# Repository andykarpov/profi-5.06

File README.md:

# Unofficial Profi 5.06 repository 

Mainboard forum: http://zx-pk.ru/threads/21644-plata-protsessora-profi-v5-06.html
Upperboard forum: http://zx-pk.ru/threads/21356-plata-periferii-profi-v5-06.html

## Ветка mega_real_spi

Данная ветка содержит экспериметнальную прошивку для CPLD и новую реализацию контроллера клавиатуры / мыши / RTC.

Отличительные особенности реализации:
- безвейтовость
- работа клавиатуы в турбо-режимах
- работа всех функциональных кнопок
- реализация профиковского стандарта XT клавиатуры и стандартного ZX Spectrum режима
- поддержка мыши (2-,3-кнопочных, со скроллером и без)
- поддержка RTC (только чтение регистров времени и даты)

Контроллер клавиатуры собран на дополнительной платке (на базе Atmega328) без доработок платы верхушки. 

## Принцип работы

Функция контроллера - получить данные от PS/2 клавиатуры и мыши и передать их по SPI протоколу в виде матрицы 
состояний механической клавиатуры ZX Spectrum + нескольких байт координат от мыши. Всю остальную работу берет на себя CPLD, моментально декодируя данные и подставляя готовые состояния при дешифрации порта #FE. Скорость потока от МК к CPLD составляет около 1кГц. Если подключена мышь - скорость потока немного снижается, но по ощущениям - это никак не влияет на скорость работы клавиатуры.

### Специальные клавиши и клавиатурные комбинации
- Scroll Lock: переключает turbo режим, значение сохраняется в энергонезависимой памяти
- Print Screen: переключает раскладку клавиатуры profi / zx spectrum
- Ctrl+Alt+Del: формирует сигнал сброса 
- Ctrl+Alt+Backpace: принудительная переинициализация контроллера
- Ctrl+Alt+Esc: кнопка Magic

### Установка даты и времени RTC часиков верхушки
Так как в контроллере не реализована эмуляция RTC в полной мере (только чтение), для установки времени можно воспользоваться последовательным соединением с контроллером.
Реализованные команды:
- HELP выведет встроенную подсказку
- GET выведет текущее время
- SET YYYY MM DD HH II SS W установит RTC в заданную дату/время/день недели

## Контроллер на базе Atmega328

Данный контроллер собирается в виде отдельной платки, которая вставляется в панельку вместо Atmega8515. Контроллер выполнен на базе МК Atmega328.Программирование осуществляется из среды Arduino IDE 1.6.1 или выше. Никакие модификации платы верхушки не требуются.

## Готовые прошивки
Готовые hex-файлы для прошивки с помощью программатора готовы и доступны из git-репозитария.

Fuse биты для Atmega328:
Low Fuse	0xFF
High Fuse	0xDA
Extended Fuse	0x05

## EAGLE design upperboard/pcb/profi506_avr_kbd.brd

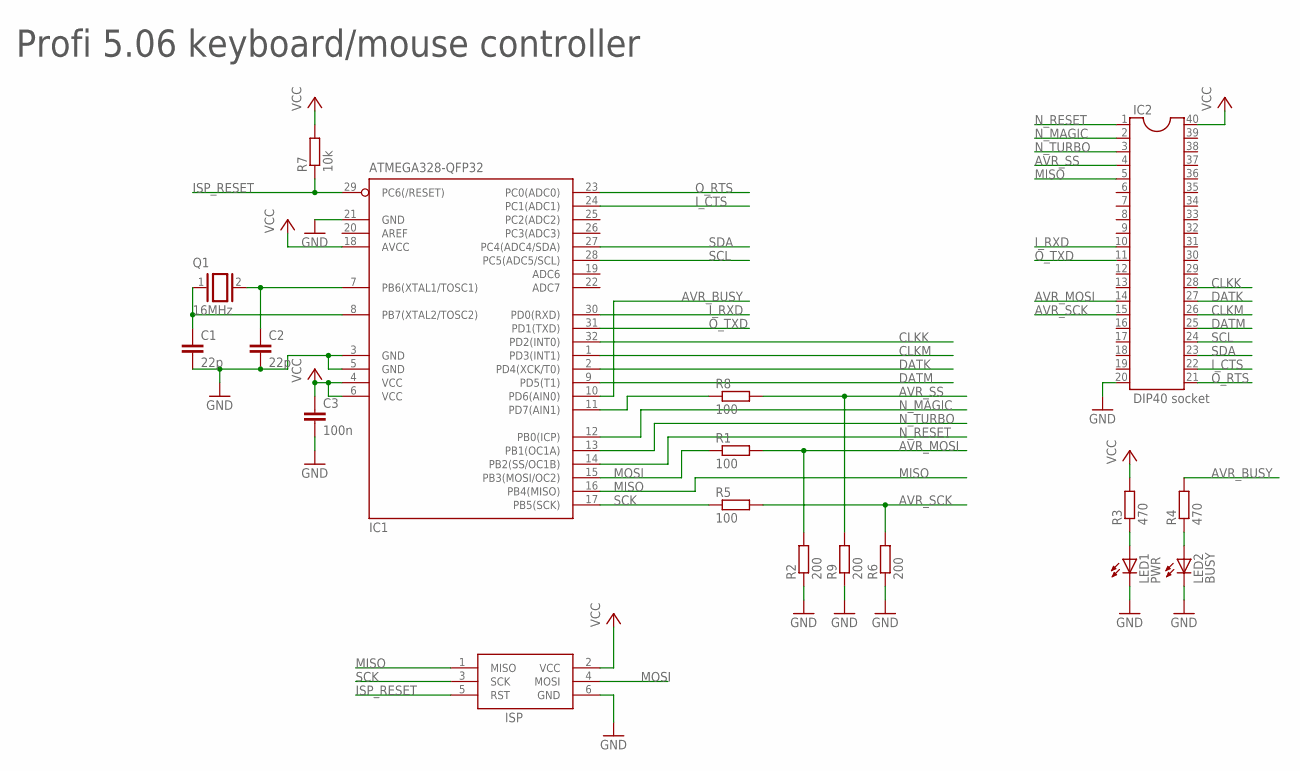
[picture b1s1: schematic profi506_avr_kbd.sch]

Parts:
C1, C2: 22p; C0805
C3: 100n; C0805
IC1: ATMEGA328-QFP32; TQFP32-08
IC2: DIP40 socket; DIL40
ISP: AVRISP-BOX
LED1: PWR; CHIPLED_0805
LED2: BUSY; CHIPLED_0805
Q1: 16MHz; QS
R1, R5, R8: 100; R0805
R2, R6, R9: 200; R0805
R3, R4: 470; R0805
R7: 10k; R0805

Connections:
AVR_BUSY: IC1.10 (PD6(AIN0)), R4.2
AVR_MOSI: IC2.14, R1.2, R2.2
AVR_SCK: IC2.15, R5.2, R6.2
AVR_SS: IC2.4, R8.2, R9.2
CLKK: IC1.32 (PD2(INT0)), IC2.28
CLKM: IC1.1 (PD3(INT1)), IC2.26
DATK: IC1.2 (PD4(XCK/T0)), IC2.27
DATM: IC1.9 (PD5(T1)), IC2.25
GND: C1.2, C2.2, C3.2, IC1.3 (GND), IC1.5 (GND), IC1.21 (GND), IC2.20, ISP.6 (GND), LED1.C, LED2.C, R2.1, R6.1, R9.1
ISP_RESET: IC1.29 (PC6(/RESET)), ISP.5 (RST), R7.1
I_CTS: IC1.24 (PC1(ADC1)), IC2.22
I_RXD: IC1.30 (PD0(RXD)), IC2.10
MISO: IC1.16 (PB4(MISO)), IC2.5, ISP.1 (MISO)
MOSI: IC1.15 (PB3(MOSI/OC2)), ISP.4 (MOSI), R1.1
unnamed: C2.1, IC1.7 (PB6(XTAL1/TOSC1)), Q1.2
unnamed: C1.1, IC1.8 (PB7(XTAL2/TOSC2)), Q1.1
unnamed: IC1.11 (PD7(AIN1)), R8.1
unnamed: LED1.A, R3.1
unnamed: LED2.A, R4.1
N_MAGIC: IC1.12 (PB0(ICP)), IC2.2
N_RESET: IC1.14 (PB2(SS/OC1B)), IC2.1
N_TURBO: IC1.13 (PB1(OC1A)), IC2.3
O_RTS: IC1.23 (PC0(ADC0)), IC2.21
O_TXD: IC1.31 (PD1(TXD)), IC2.11
SCK: IC1.17 (PB5(SCK)), ISP.3 (SCK), R5.1
SCL: IC1.28 (PC5(ADC5/SCL)), IC2.24
SDA: IC1.27 (PC4(ADC4/SDA)), IC2.23
VCC: C3.1, IC1.4 (VCC), IC1.6 (VCC), IC1.18 (AVCC), IC2.40, ISP.2 (VCC), R3.2, R7.2

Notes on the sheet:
Profi 5.06 keyboard/mouse controller

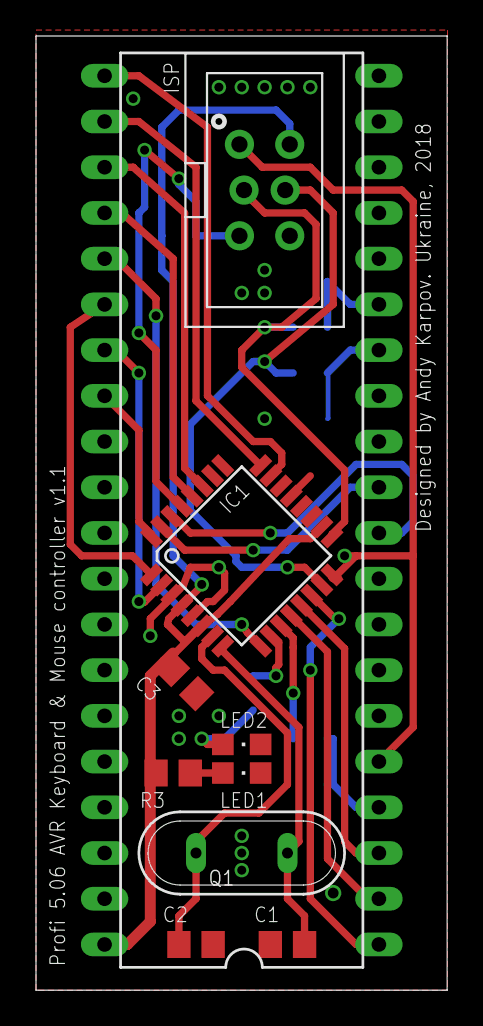
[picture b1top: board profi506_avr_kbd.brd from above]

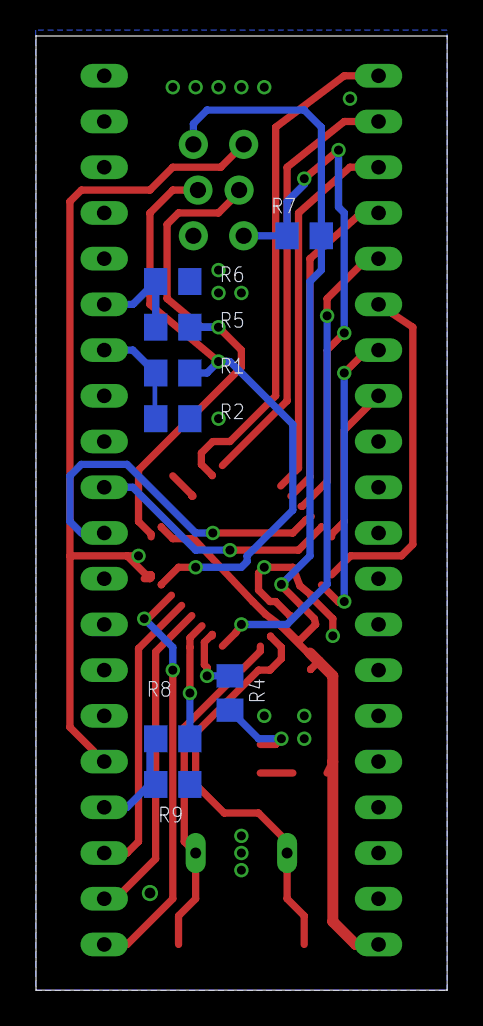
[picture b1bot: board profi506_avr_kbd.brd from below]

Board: 2 copper layers, 22.8 x 53.0 mm, 19 parts (8 on the bottom side), 28 nets.

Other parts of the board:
U$1: OSHWLOGO_TOL_0.2

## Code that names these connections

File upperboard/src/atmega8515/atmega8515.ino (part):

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#define DEBUG_MODE 1

// ---- Pins for Atmega328 ----
#define PIN_KBD_CLK 2 // pin 28 (CLKK)
#define PIN_KBD_DAT 4 // pin 27 (DATK)

#define PIN_MOUSE_CLK 3 // pin 26 (CLKM)
#define PIN_MOUSE_DAT 5 // pin 25 (DATM)

#define PIN_AVR_CLK 11 // pin 14 (ATM_ADR0 - CPLD PIN 102)
#define PIN_AVR_RST 12 // pin 5 (ATM_PB4 - CPLD PIN 123)
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// Profi upper board modifications:
// 1) replace crystal with 16MHz
// 2) add wire between D34:28 and D34:13
#define PIN_KBD_CLK_ORIG 23 // pin 28 (CLKK)
#define PIN_KBD_CLK 11 // pin 13 must be connected to pin 28.
#define PIN_KBD_DAT 22 // pin 27 (DATK)

#define PIN_MOUSE_CLK 21 // pin 26 (CLKM)
#define PIN_MOUSE_DAT 20 // pin 25 (DATM)

#define PIN_AVR_CLK 12 // pin 14 (ATM_ADR0 - CPLD PIN 102)
#define PIN_AVR_RST 4 // pin 5 (ATM_PB4 - CPLD PIN 123)
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
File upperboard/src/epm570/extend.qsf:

# -------------------------------------------------------------------------- #
#
# Copyright (C) 1991-2009 Altera Corporation
# Your use of Altera Corporation's design tools, logic functions 
# and other software and tools, and its AMPP partner logic 
# functions, and any output files from any of the foregoing 
# (including device programming or simulation files), and any 
# associated documentation or information are expressly subject 
# to the terms and conditions of the Altera Program License 
# Subscription Agreement, Altera MegaCore Function License 
# Agreement, or other applicable license agreement, including, 
# without limitation, that your use is for the sole purpose of 
# programming logic devices manufactured by Altera and sold by 
# Altera or its authorized distributors.  Please refer to the 
# applicable agreement for further details.
#
# -------------------------------------------------------------------------- #
#
# Quartus II
# Version 9.1 Build 222 10/21/2009 SJ Full Version
# Date created = 16:20:46  August 09, 2012
#
# -------------------------------------------------------------------------- #
#
# Notes:
#
# 1) The default values for assignments are stored in the file:
#		extend_assignment_defaults.qdf
#    If this file doesn't exist, see file:
#		assignment_defaults.qdf
#
# 2) Altera recommends that you do not modify this file. This
#    file is updated automatically by the Quartus II software
#    and any changes you make may be lost or overwritten.
#
# -------------------------------------------------------------------------- #


set_global_assignment -name FAMILY "MAX II"
set_global_assignment -name DEVICE EPM570T144C5
set_global_assignment -name TOP_LEVEL_ENTITY extend
set_global_assignment -name ORIGINAL_QUARTUS_VERSION 9.1
set_global_assignment -name PROJECT_CREATION_TIME_DATE "16:20:46  AUGUST 09, 2012"
set_global_assignment -name LAST_QUARTUS_VERSION "13.0 SP1"
set_global_assignment -name USE_GENERATED_PHYSICAL_CONSTRAINTS OFF -section_id eda_blast_fpga
set_global_assignment -name DEVICE_FILTER_PACKAGE TQFP
set_global_assignment -name DEVICE_FILTER_PIN_COUNT 144
set_global_assignment -name DEVICE_FILTER_SPEED_GRADE 5
set_global_assignment -name MAX7000_DEVICE_IO_STANDARD "3.3-V LVTTL"
set_location_assignment PIN_2 -to reset
set_location_assignment PIN_98 -to nmi
set_location_assignment PIN_85 -to intr
set_location_assignment PIN_75 -to cswg
set_location_assignment PIN_84 -to drq
set_location_assignment PIN_74 -to dden
set_location_assignment PIN_73 -to wf_de
set_location_assignment PIN_80 -to wd
set_location_assignment PIN_79 -to tr43
set_location_assignment PIN_72 -to rawr
set_location_assignment PIN_71 -to rclk
set_location_assignment PIN_70 -to wg_clk
set_location_assignment PIN_69 -to hlt
set_location_assignment PIN_78 -to sl
set_location_assignment PIN_77 -to sr
set_location_assignment PIN_76 -to rst
set_location_assignment PIN_81 -to rdat
set_location_assignment PIN_68 -to side1
set_location_assignment PIN_67 -to wdat
set_location_assignment PIN_66 -to disk1
set_location_assignment PIN_63 -to disk0
set_location_assignment PIN_45 -to bc1a
set_location_assignment PIN_49 -to bdira
set_location_assignment PIN_48 -to bc1b
set_location_assignment PIN_50 -to bdirb
set_location_assignment PIN_91 -to magik
set_location_assignment PIN_86 -to f8
set_location_assignment PIN_130 -to SD_CLK
set_location_assignment PIN_95 -to w_a_i_t
set_global_assignment -name SYNTH_TIMING_DRIVEN_SYNTHESIS OFF
set_global_assignment -name OPTIMIZE_HOLD_TIMING OFF
set_global_assignment -name FITTER_EFFORT "STANDARD FIT"
set_location_assignment PIN_31 -to Data[0]
set_location_assignment PIN_30 -to Data[1]
set_location_assignment PIN_29 -to Data[2]
set_location_assignment PIN_24 -to Data[3]
set_location_assignment PIN_23 -to Data[4]
set_location_assignment PIN_27 -to Data[5]
set_location_assignment PIN_28 -to Data[6]
set_location_assignment PIN_32 -to Data[7]
set_location_assignment PIN_13 -to adress[0]
set_location_assignment PIN_12 -to adress[1]
set_location_assignment PIN_11 -to adress[2]
set_location_assignment PIN_8 -to adress[3]
set_location_assignment PIN_141 -to adress[4]
set_location_assignment PIN_142 -to adress[5]
set_location_assignment PIN_143 -to adress[6]
set_location_assignment PIN_144 -to adress[7]
set_location_assignment PIN_139 -to adress[8]
set_location_assignment PIN_138 -to adress[9]
set_location_assignment PIN_137 -to adress[10]
set_location_assignment PIN_15 -to adress[12]
set_location_assignment PIN_134 -to adress[11]
set_location_assignment PIN_16 -to adress[13]
set_location_assignment PIN_18 -to adress[14]
set_location_assignment PIN_20 -to adress[15]
set_location_assignment PIN_97 -to iorqge
set_global_assignment -name MIN_CORE_JUNCTION_TEMP 0
set_global_assignment -name MAX_CORE_JUNCTION_TEMP 85
set_global_assignment -name POWER_EXT_SUPPLY_VOLTAGE_TO_REGULATOR 3.3V
set_global_assignment -name INCREMENTAL_COMPILATION OFF
set_global_assignment -name LL_ROOT_REGION ON -section_id "Root Region"
set_global_assignment -name LL_MEMBER_STATE LOCKED -section_id "Root Region"
set_global_assignment -name STRATIX_DEVICE_IO_STANDARD "3.3-V LVTTL"
set_location_assignment PIN_6 -to rom14
set_location_assignment PIN_1 -to cpm
set_location_assignment PIN_21 -to t_ap6
set_location_assignment PIN_22 -to oe_ap6
set_location_assignment PIN_37 -to t_lvc245
set_location_assignment PIN_38 -to saa_cs
set_location_assignment PIN_39 -to saa_a0
set_location_assignment PIN_40 -to saa_clk
set_location_assignment PIN_41 -to dac2_cs
set_location_assignment PIN_42 -to dac
set_location_assignment PIN_43 -to dac1_cs
set_location_assignment PIN_44 -to vv55_cs
set_location_assignment PIN_52 -to blok
set_location_assignment PIN_53 -to cache_we
set_location_assignment PIN_55 -to lwr
set_location_assignment PIN_57 -to vi53_cs
set_location_assignment PIN_59 -to ladr5
set_location_assignment PIN_58 -to ladr6
set_location_assignment PIN_60 -to vv51_cs
set_location_assignment PIN_61 -to rxrdt
set_location_assignment PIN_62 -to txrdt
set_location_assignment PIN_87 -to timer
set_location_assignment PIN_93 -to ri
set_location_assignment PIN_94 -to dcd
set_location_assignment PIN_104 -to SEL
set_location_assignment PIN_105 -to INT0
set_location_assignment PIN_96 -to int
set_location_assignment PIN_106 -to hdd_a0
set_location_assignment PIN_107 -to hdd_a1
set_location_assignment PIN_108 -to hdd_a2
set_location_assignment PIN_109 -to hdd_wr
set_location_assignment PIN_110 -to hdd_cs1
set_location_assignment PIN_111 -to hdd_cs0
set_location_assignment PIN_112 -to hdd_rd
set_location_assignment PIN_113 -to hdd_rh_oe
set_location_assignment PIN_114 -to hdd_rh_c
set_location_assignment PIN_117 -to hdd_wh_oe
set_location_assignment PIN_118 -to hdd_wh_c
set_location_assignment PIN_119 -to hdd_rwl_t
set_location_assignment PIN_120 -to c_dffd
set_location_assignment PIN_127 -to turbo
set_location_assignment PIN_14 -to zx14mhz
set_location_assignment PIN_133 -to tr_dos
set_location_assignment PIN_129 -to SD_DO
set_location_assignment PIN_132 -to SD_CS
set_location_assignment PIN_131 -to SD_DI
set_location_assignment PIN_3 -to wr_z
set_location_assignment PIN_4 -to rd_z
set_location_assignment PIN_7 -to mrq_z
set_location_assignment PIN_5 -to iorq_z
set_location_assignment PIN_140 -to m1_z
set_location_assignment PIN_124 -to iorqge_sl
set_location_assignment PIN_51 -to cache_oe
set_location_assignment PIN_122 -to ay_clk
set_location_assignment PIN_121 -to cpld_121

set_location_assignment PIN_101 -to INT1
set_global_assignment -name POWER_PRESET_COOLING_SOLUTION "NO HEAT SINK WITH STILL AIR"
set_location_assignment PIN_125 -to AVR_SS
set_location_assignment PIN_123 -to AVR_MISO
set_location_assignment PIN_102 -to AVR_MOSI
set_location_assignment PIN_103 -to AVR_SCK
set_global_assignment -name VHDL_FILE mc146818a.vhd
set_global_assignment -name VHDL_FILE spi_slave.vhd
set_global_assignment -name VHDL_FILE cpld_kbd.vhd
set_global_assignment -name VHDL_FILE SPI.vhd
set_global_assignment -name VHDL_FILE extend.vhd
set_global_assignment -name VECTOR_WAVEFORM_FILE extend.vwf

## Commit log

2018-03-20 Updated upperboard pdf, renamed zxmc2 firmware hex, added upperboard pcb sources
2018-03-20 added links to the forums
2018-03-20 Expiremental functionality: reading ports 7ffd and dffd from trdos
2018-03-20 Expirimental branch to decode keyboard on cpld side, atmega firmware will be rewritten
2018-03-20 Experimental branch with cutted out Atmega8515 support
2018-03-20 Experimenail branch with mouse support inside CPLD without atmega
2018-03-20 added pcb revisions RevA and RevB
2018-03-21 Merge
2018-03-25 Added implementation of atmega328p replacement for ps/2 keyboard / mouse controller. Initial revision
2018-03-26 port FE selector fixes
2018-03-26 fixed port FE
2018-03-26 fixed kb decoding
2018-03-26 added clock and cs to cpld_kbd
2018-03-26 fixed bug :)
2018-03-26 latest firmware
2018-03-26 fixed profi keyboard decoding
2018-03-27 added turbo, mode change and reset
2018-03-28 Added pin INT1 as input
2018-03-28 Changed mouse data packet structure
2018-03-28 Disabled serial output
2018-03-28 Добавлена поддержка чтения мыши
2018-03-29 added mouse support
2018-03-29 fixed mouse buttons
2018-03-29 Fixed mouse signed -> unsigned conversion
2018-03-29 refactoring
2018-03-29 Added conditions to automatically compile code for both Atmega328 and Atmega8515
2018-03-29 added binaries for atmega8515
2018-03-29 Добавлена схема и плата для контроллера на базе Atmega328p
2018-03-29 fixed gerbers
2018-03-31 Added active 0 for AVR->CPLD communication
2018-04-06 port #FE return Z state when no keypress from ps/2 keyboard to avoid conflicts with bottom board
2018-04-06 added more chips to support (atmega 8 / 48 / 88 / 168 / 328)
2018-04-06 updated firmware
2018-04-06 added comments
2018-04-19 added up to 5 tries to init mouse every 5s if not present
2018-05-19 implemented SPI protocol for communication
2018-05-19 missing file
2018-05-19 refactored spi transmission, renamed signals, improved speed
2018-05-19 new pcb v1.1 for avr kbd controller, added CS signal, added leds to indicate power status and activity
2018-07-16 Added library for PCF8583
2018-07-16 feature: added reset on boot, some improvements to BUSY led
2018-07-18 Changed EPM570 firmware: removed m1 from oe_ap6
2018-07-19 Added SEL=0 to avoid data bus interference from DD37
2018-07-19 New firmware build 2018-07-19
2018-07-19 правильное чтение 6-го бита XT клавиатуры из порта FE
2018-07-19 Убран сигнал M1 при декодировании порта FE
2018-07-19 Упрощена передача бита 6 порта FE
2018-07-20 Добавлено сохранение и восстановление параметров режима клавиатуры и сосояния Turbo
2018-07-20 Изменения в опросе 6-го бита порта FE
2018-07-21 Добавлен вывод 7 бита порта dffd на cpld_121
2018-07-21 new firmware
2018-07-21 Добавлен селектор режима (speccy / profi) через внешнюю ногу, на которой раньше висела перемычка INVERSE_RGBI
2018-07-22 added initial RTC support
2018-07-22 Added support to set RTC via Serial
2018-07-23 Убрана возможность уствновки времени в RTC
2018-07-23 Добавлена передача и установка дня недели
2018-08-20 Fixed extended keys with shift
2018-12-24 Added magic button by Ctrl+Alt+Esc
2018-12-24 Fixed readme
